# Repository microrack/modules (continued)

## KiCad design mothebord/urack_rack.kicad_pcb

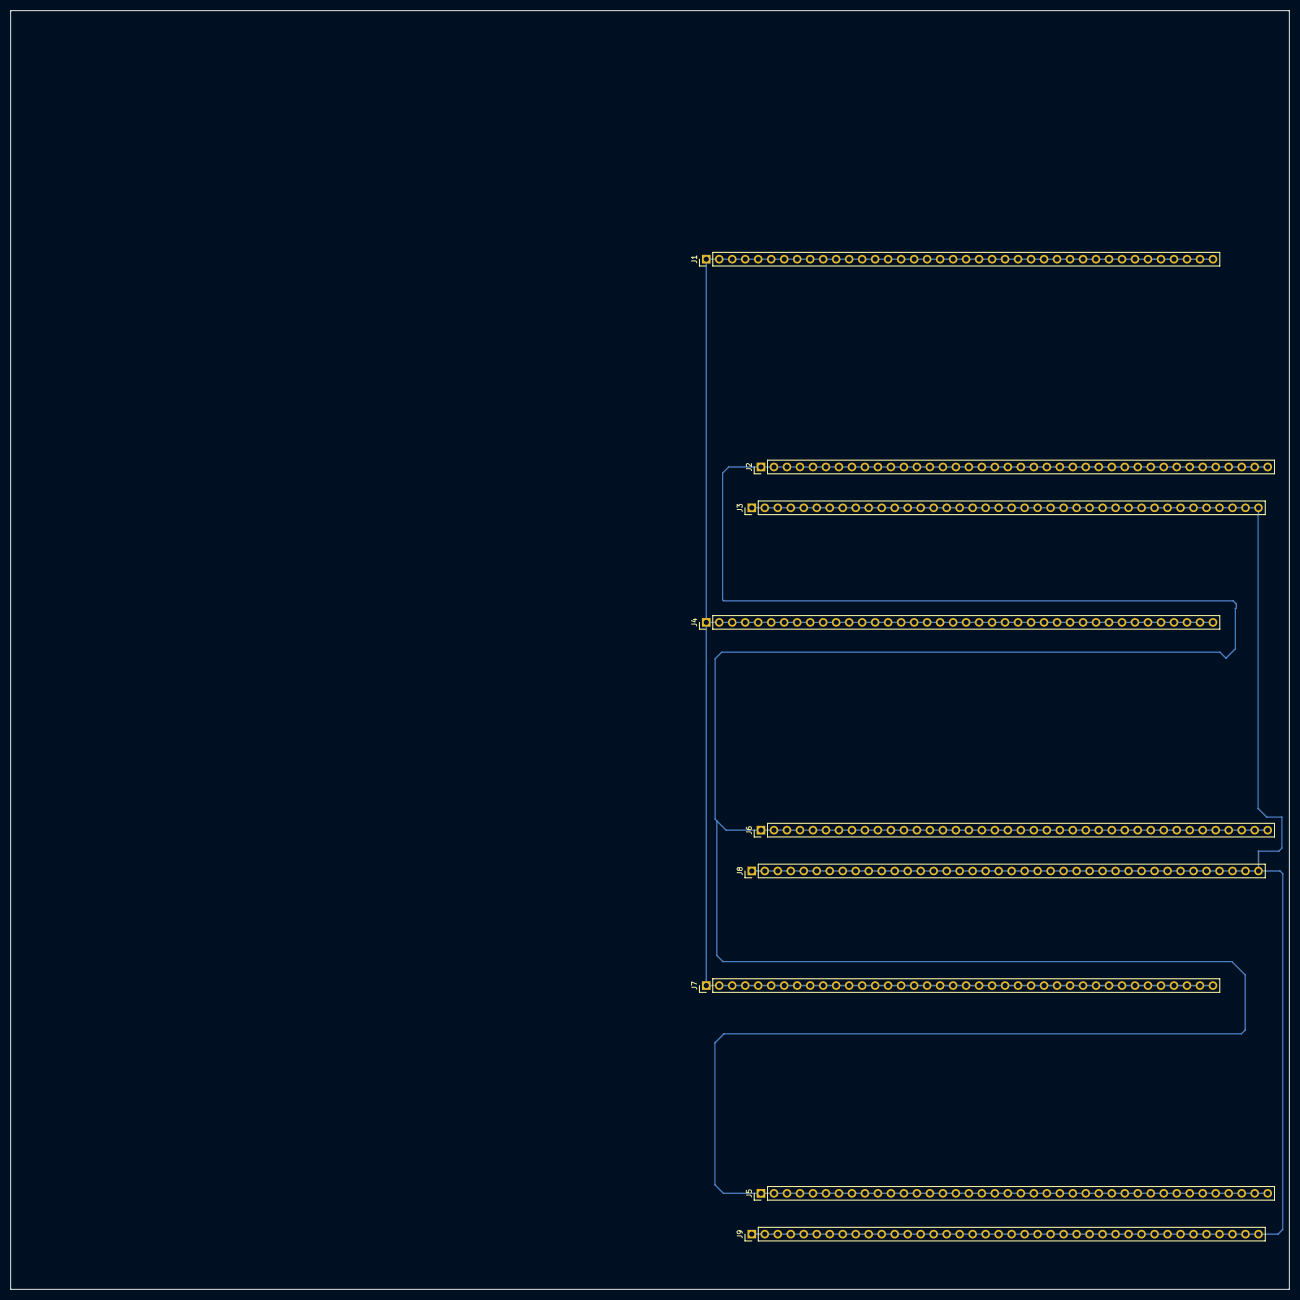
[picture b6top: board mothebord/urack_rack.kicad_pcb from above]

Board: 2 copper layers, 250.0 x 250.0 mm, 9 parts (0 on the bottom side), 3 nets.

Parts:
J1, J2, J3, J4, J5, J6, J7, J8, J9: Conn_01x40; Pin_Header_Straight_1x40_Pitch2.54mm

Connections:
+5V: J1.1, J1.2, J1.3, J1.4, J1.5, J1.6, J1.7, J1.8, J1.9, J1.10, J1.11, J1.12, J1.13, J1.14, J1.15, J1.16, J1.17, J1.18, J1.19, J1.20, J1.21, J1.22, J1.23, J1.24, J1.25, J1.26, J1.27, J1.28, J1.29, J1.30, J1.31, J1.32, J1.33, J1.34, J1.35, J1.36, J1.37, J1.38, J1.39, J1.40, J4.1, J4.2, J4.3, J4.4, J4.5, J4.6, J4.7, J4.8, J4.9, J4.10, J4.11, J4.12, J4.13, J4.14, J4.15, J4.16, J4.17, J4.18, J4.19, J4.20, J4.21, J4.22, J4.23, J4.24, J4.25, J4.26, J4.27, J4.28, J4.29, J4.30, J4.31, J4.32, J4.33, J4.34, J4.35, J4.36, J4.37, J4.38, J4.39, J4.40, J7.1, J7.2, J7.3, J7.4, J7.5, J7.6, J7.7, J7.8, J7.9, J7.10, J7.11, J7.12, J7.13, J7.14, J7.15, J7.16, J7.17, J7.18, J7.19, J7.20, J7.21, J7.22, J7.23, J7.24, J7.25, J7.26, J7.27, J7.28, J7.29, J7.30, J7.31, J7.32, J7.33, J7.34, J7.35, J7.36, J7.37, J7.38, J7.39, J7.40
-5V: J2.1, J2.2, J2.3, J2.4, J2.5, J2.6, J2.7, J2.8, J2.9, J2.10, J2.11, J2.12, J2.13, J2.14, J2.15, J2.16, J2.17, J2.18, J2.19, J2.20, J2.21, J2.22, J2.23, J2.24, J2.25, J2.26, J2.27, J2.28, J2.29, J2.30, J2.31, J2.32, J2.33, J2.34, J2.35, J2.36, J2.37, J2.38, J2.39, J2.40, J5.1, J5.2, J5.3, J5.4, J5.5, J5.6, J5.7, J5.8, J5.9, J5.10, J5.11, J5.12, J5.13, J5.14, J5.15, J5.16, J5.17, J5.18, J5.19, J5.20, J5.21, J5.22, J5.23, J5.24, J5.25, J5.26, J5.27, J5.28, J5.29, J5.30, J5.31, J5.32, J5.33, J5.34, J5.35, J5.36, J5.37, J5.38, J5.39, J5.40, J6.1, J6.2, J6.3, J6.4, J6.5, J6.6, J6.7, J6.8, J6.9, J6.10, J6.11, J6.12, J6.13, J6.14, J6.15, J6.16, J6.17, J6.18, J6.19, J6.20, J6.21, J6.22, J6.23, J6.24, J6.25, J6.26, J6.27, J6.28, J6.29, J6.30, J6.31, J6.32, J6.33, J6.34, J6.35, J6.36, J6.37, J6.38, J6.39, J6.40
GNDREF: J3.1, J3.2, J3.3, J3.4, J3.5, J3.6, J3.7, J3.8, J3.9, J3.10, J3.11, J3.12, J3.13, J3.14, J3.15, J3.16, J3.17, J3.18, J3.19, J3.20, J3.21, J3.22, J3.23, J3.24, J3.25, J3.26, J3.27, J3.28, J3.29, J3.30, J3.31, J3.32, J3.33, J3.34, J3.35, J3.36, J3.37, J3.38, J3.39, J3.40, J8.1, J8.2, J8.3, J8.4, J8.5, J8.6, J8.7, J8.8, J8.9, J8.10, J8.11, J8.12, J8.13, J8.14, J8.15, J8.16, J8.17, J8.18, J8.19, J8.20, J8.21, J8.22, J8.23, J8.24, J8.25, J8.26, J8.27, J8.28, J8.29, J8.30, J8.31, J8.32, J8.33, J8.34, J8.35, J8.36, J8.37, J8.38, J8.39, J8.40, J9.1, J9.2, J9.3, J9.4, J9.5, J9.6, J9.7, J9.8, J9.9, J9.10, J9.11, J9.12, J9.13, J9.14, J9.15, J9.16, J9.17, J9.18, J9.19, J9.20, J9.21, J9.22, J9.23, J9.24, J9.25, J9.26, J9.27, J9.28, J9.29, J9.30, J9.31, J9.32, J9.33, J9.34, J9.35, J9.36, J9.37, J9.38, J9.39, J9.40

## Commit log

2019-02-03 init
2019-02-03 add VCO model
2019-02-03 add VCF model
2019-02-03 add VCA
2019-02-03 add envelope generator
2019-02-16 add sequencer bulk pcb
2019-02-22 New schematics Kicad.
2019-02-24 New edit schems, add net lists, pcb files and library
2019-03-02 Изменены библиотеки. Добавлинны библиотеки примененные в проекте локально. Добавленны заготовки для печатных плат. Добавленны 3D модели компоненток.
2019-03-03 fix relative path, fix lib path in VCO
2019-03-03 add library
2019-03-05 Исправленну ошибки в схемах. Полностью локальные библиотеки и 3D модели.
2019-03-05 Исправленны ошибки в схемах. Локальные библиотеки для проекта и 3D модели.
2019-03-05 Исправленны ошибки в схемах.
2019-03-14 ADD PCB module VCO. ADD folder MOTHEBORD.
2019-03-28 Изменение в схемах. Разведенны ПП
2025-12-24 Change icon
2025-12-25 in-63
2025-12-25 midi
2025-12-25 saturator
2025-12-25 sequencer
2025-12-25 noise
2025-12-25 outs
2025-12-25 jacket
2025-12-25 Update module name
2025-12-27 add schematics
2026-01-06 add pdf schematics
2026-01-06 add license files
2026-01-06 add schematic links
2026-01-08 add mod-pwr readme
2026-01-08 add chassis readme
2026-01-08 add images
2026-01-08 update mod-pwr image
2026-01-08 update chassis image
2026-01-08 add mod-pwr pins description
2026-01-08 add mod-pwr images
2026-01-08 update mod-pwr readme
2026-01-08 remove outdated schematics link
2026-01-08 update chassis readme
2026-02-07 Add flasher link
2026-02-07 Fix chassis docs
2026-02-07 Fix pics width
2026-02-07 github source link
2026-02-07 power and chassis in root
2026-02-07 add product page links
2026-02-08 add forum links
2026-02-08 emoji for links list
2026-02-08 separate forum thread for each module
2026-02-08 update index link names, remove mod- prefixes
